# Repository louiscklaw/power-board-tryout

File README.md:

# A Simple PCB for getting various voltage(e.g. 3V3, 5V, 8V etc...) from one voltage source

### Purpose

My power supply capable a single channel voltage source only. If I need another voltage value (e.g. 3V3 on a 12V board). There is no change for me to do so using my power supply. So i create this board to let me get another voltage values(e.g. 3V3, 5V, etc...) from the main power supply (12V).

### PCB outlook

####  This is the front side

####  This is the back side

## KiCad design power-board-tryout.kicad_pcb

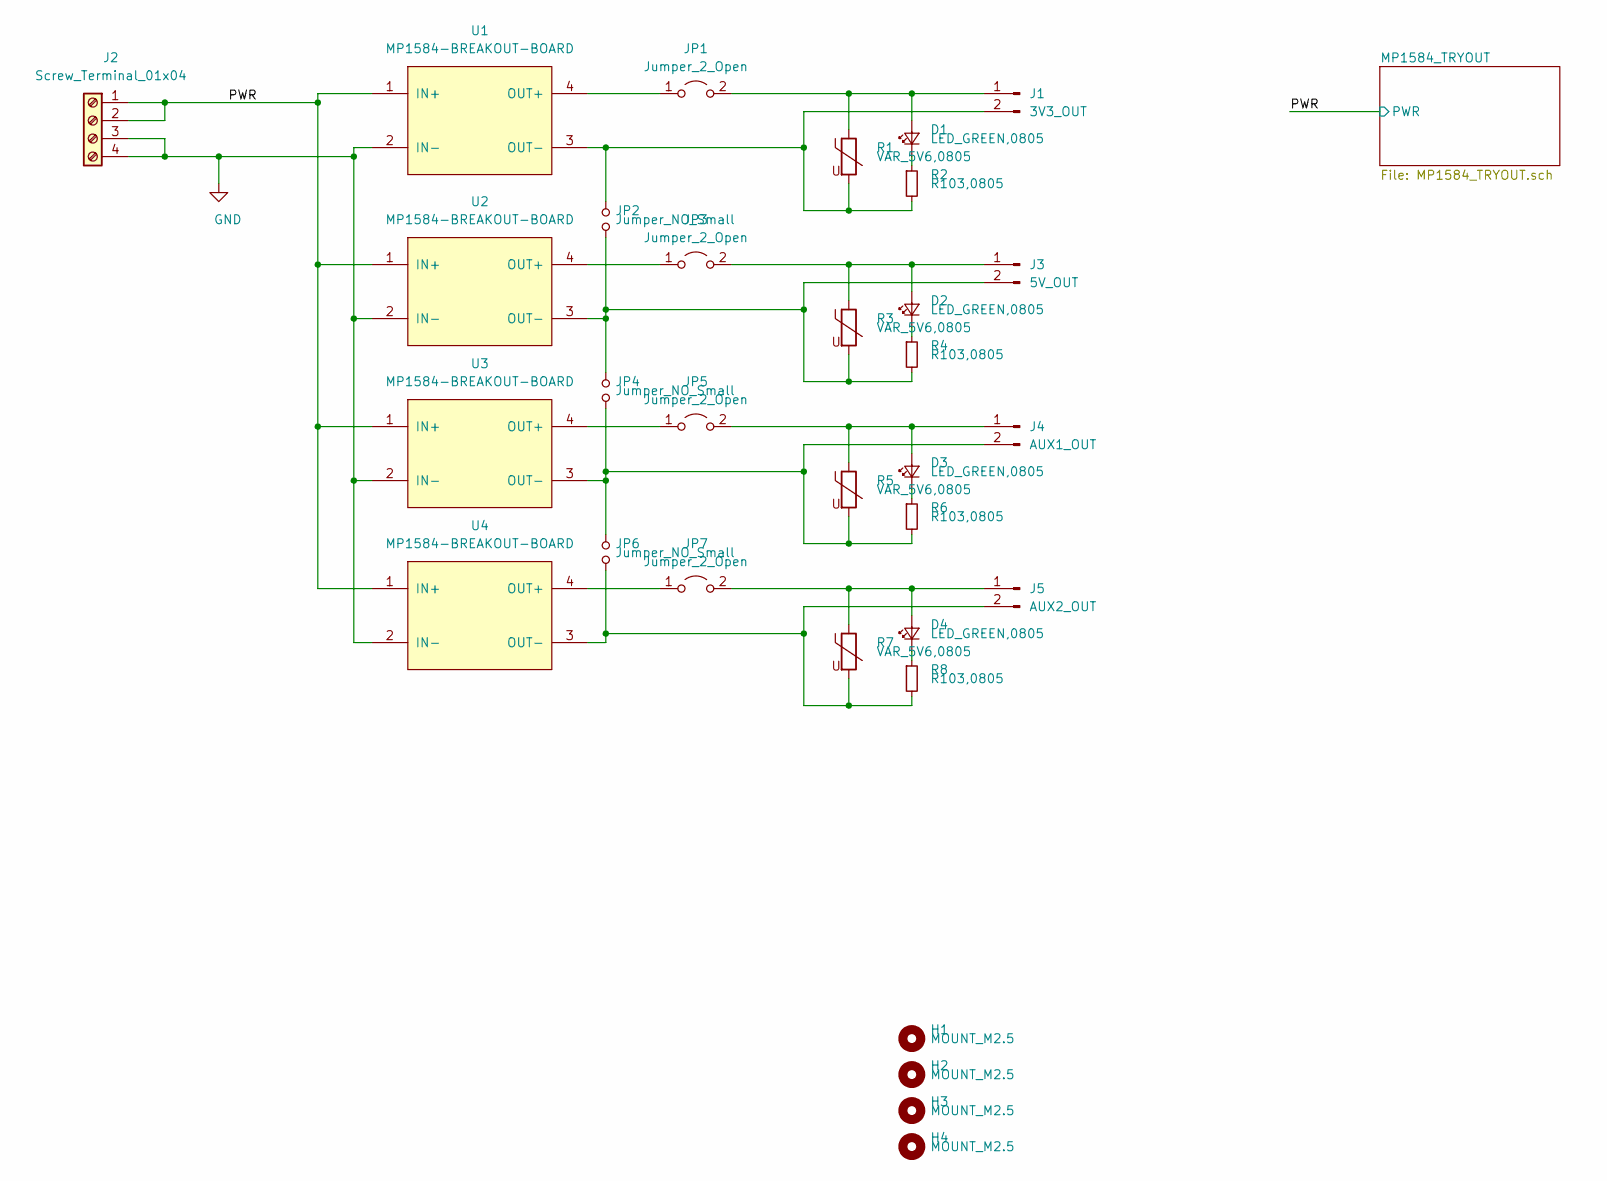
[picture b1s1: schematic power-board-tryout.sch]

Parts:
D1, D2, D3, D4: LED_GREEN,0805; LED_0805_2012Metric
H1, H2, H3, H4: MOUNT_M2.5; MountingHole_2.7mm_M2.5,rpi_like
J1: 3V3_OUT; PinHeader_1x02_P2.54mm_power_output_terminal
J2: Screw_Terminal_01x04; PinHeader_1x04_P2.54mm_Vertical
J3: 5V_OUT; PinHeader_1x02_P2.54mm_power_output_terminal
J4: AUX1_OUT; PinHeader_1x02_P2.54mm_power_output_terminal
J5: AUX2_OUT; PinHeader_1x02_P2.54mm_power_output_terminal
JP1, JP3, JP5, JP7: Jumper_2_Open; SolderJumper-2_P1.3mm_Open_TrianglePad1.0x1.5mm
JP2, JP4, JP6: Jumper_NO_Small; SolderJumper-2_P1.3mm_Open_TrianglePad1.0x1.5mm
R1, R3, R5, R7: VAR_5V6,0805; VAR_0805
R2, R4, R6, R8: R103,0805; R_0805_2012Metric_Pad1.15x1.40mm_HandSolder
U1, U2, U3, U4: MP1584-BREAKOUT-BOARD; MP1584_buck_module

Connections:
/PWR: J2.1, J2.2, U1.1 (IN+), U2.1 (IN+), U3.1 (IN+), U4.1 (IN+); also elsewhere on the board
GND: J2.3, J2.4, U1.2 (IN-), U2.2 (IN-), U3.2 (IN-), U4.2 (IN-); also elsewhere on the board
unnamed: D1.1 (K), R2.1
unnamed: D1.2 (A), J1.1, JP1.2 (B), R1.1
unnamed: D2.1 (K), R4.1
unnamed: D2.2 (A), J3.1, JP3.2 (B), R3.1
unnamed: D3.1 (K), R6.1
unnamed: D3.2 (A), J4.1, JP5.2 (B), R5.1
unnamed: D4.1 (K), R8.1
unnamed: D4.2 (A), J5.1, JP7.2 (B), R7.1
unnamed: J1.2, JP2.1, R1.2, R2.2, U1.3 (OUT-)
unnamed: J3.2, JP2.2, JP4.1, R3.2, R4.2, U2.3 (OUT-)
unnamed: J4.2, JP4.2, JP6.1, R5.2, R6.2, U3.3 (OUT-)
unnamed: J5.2, JP6.2, R7.2, R8.2, U4.3 (OUT-)
unnamed: JP1.1 (A), U1.4 (OUT+)
unnamed: JP3.1 (A), U2.4 (OUT+)
unnamed: JP5.1 (A), U3.4 (OUT+)
unnamed: JP7.1 (A), U4.4 (OUT+)

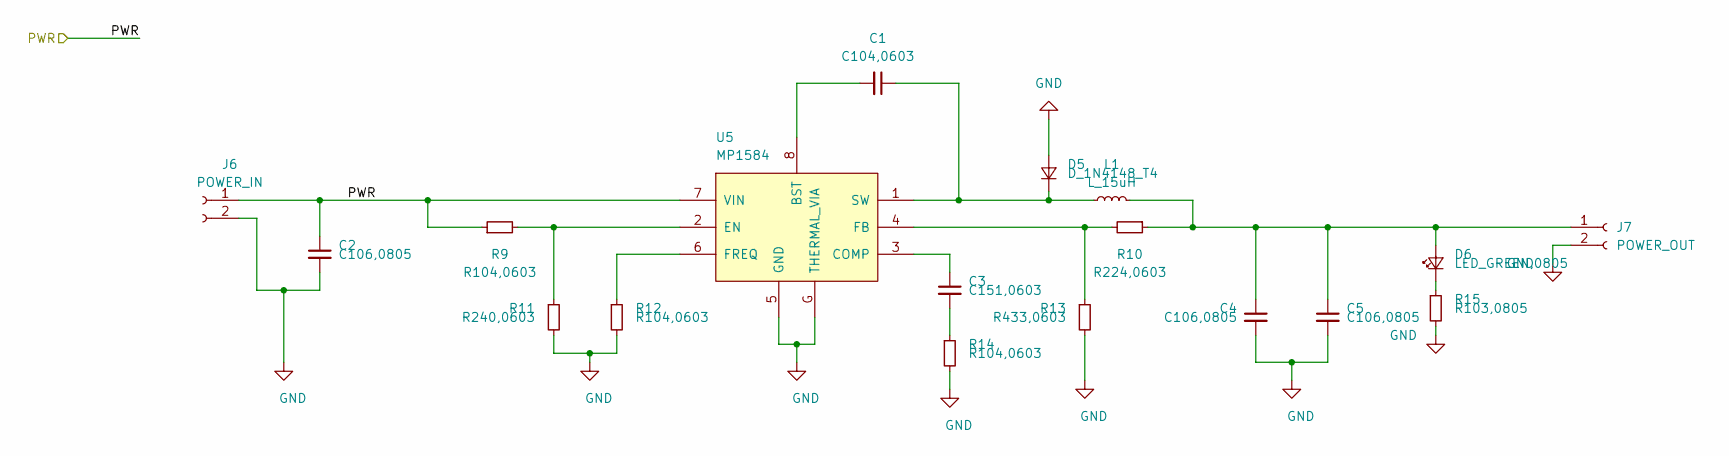
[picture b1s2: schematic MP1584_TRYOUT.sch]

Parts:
C1: C104,0603; C_0603_1608Metric_Pad1.05x0.95mm_HandSolder
C2, C4, C5: C106,0805; C_0805_2012Metric_Pad1.15x1.40mm_HandSolder
C3: C151,0603; C_0603_1608Metric_Pad1.05x0.95mm_HandSolder
D5: D_1N4148_T4; D_SOD-123
D6: LED_GREEN,0805; LED_0805_2012Metric
J6: POWER_IN; PinHeader_1x02_P2.54mm_Vertical
J7: POWER_OUT; PinHeader_1x02_P2.54mm_Vertical
L1: L_15uH; inductor_smd_6.8x3.8mm
R9, R12, R14: R104,0603; R_0603_1608Metric_Pad1.05x0.95mm_HandSolder
R10: R224,0603; R_0603_1608Metric_Pad1.05x0.95mm_HandSolder
R11: R240,0603; R_0603_1608Metric_Pad1.05x0.95mm_HandSolder
R13: R433,0603; R_0603_1608Metric_Pad1.05x0.95mm_HandSolder
R15: R103,0805; R_0805_2012Metric_Pad1.15x1.40mm_HandSolder
U5: MP1584; MP1584,SOIC-8_3.9x4.9mm_P1.27mm,thermal_via

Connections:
/PWR: C2.1, J6.1, R9.1, U5.7 (VIN); also elsewhere on the board
GND: C2.2, C4.2, C5.2, D5.2 (A), J6.2, J7.2, R11.2, R12.2, R13.2, R14.2, R15.2, U5.5 (GND), U5.G (THERMAL_VIA); also elsewhere on the board
unnamed: C1.1, D5.1 (K), L1.1, U5.1 (SW)
unnamed: C1.2, U5.8 (BST)
unnamed: C3.1, U5.3 (COMP)
unnamed: C3.2, R14.1
unnamed: C4.1, C5.1, D6.2 (A), J7.1, L1.2, R10.1
unnamed: D6.1 (K), R15.1
unnamed: R10.2, R13.1, U5.4 (FB)
unnamed: R9.2, R11.1, U5.2 (EN)
unnamed: R12.1, U5.6 (FREQ)

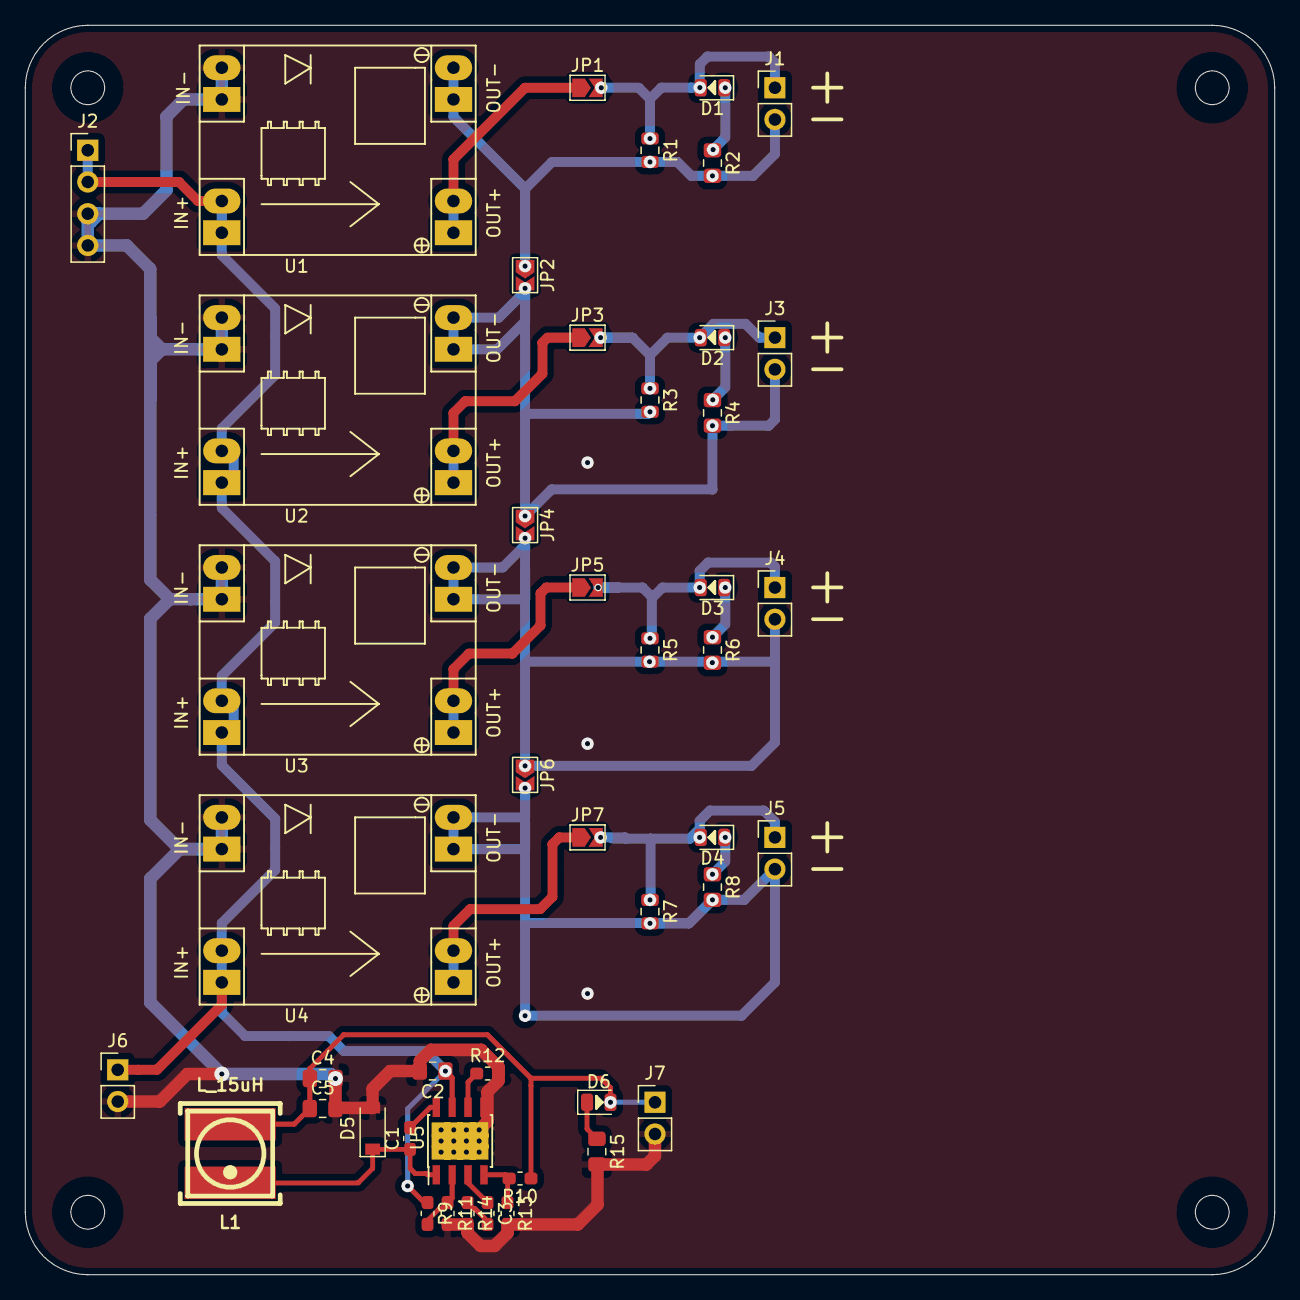
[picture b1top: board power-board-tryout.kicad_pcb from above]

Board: 2 copper layers, 100.0 x 100.0 mm, 50 parts (0 on the bottom side), 27 nets.

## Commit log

2019-05-20 init commit,
2019-05-20 update,
2019-05-25 DRC ok,
2019-05-25 update led on MP1584 and DRC ok,
2019-05-25 update README, update to fabrication,
2019-05-25 update image link,
2019-05-27 remove old temp file,
2019-05-27 update to ignore temp file,
2019-06-02 iupdate,
2020-05-05 ci: init travis build config,
2020-05-05 ci: init travis token,
